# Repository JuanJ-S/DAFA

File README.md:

# DAFA
Dispositivo de Análisis de Fugas de Agua
# Integrantes
 - Wilson David Cortes Gonzales
 - Juan Camilo Forero Castillo
 - Andres Felipe Martinez Roa
 - Fedor Santiago Palacios Hernandez
 - Juan José Santos Pineda
 - David Valero Garzon
# Descripción
Conjunto de sensores conectados a un microcontrolador central (ESP32), que monitorean el caudal y presión del agua en puntos especificos de un sistema de tuberias. El ESP32 se conecta mediante wifi a Blynk, en donde analizan los datos dados por los sensores y se determina si estan dentro de los limites establecidos. Si los valores estan por debajo de lo permitido, se interpreta una posible fuga o conexión no registrada en el sistema, lo cual hará que el dispositivo de una alerta.
# Palabras Clave
 - Perdida de Agua
 - Internet de las Cosas
 - Sensores 
 - ESP 32
 - Gestión Hídrica
 - Sostenibilidad
# Poster
Pendiente -> ¿Como que poster :c?
# Banner de Implementación del Proyecto
En proceso. Imagen preliminar

# Video del Proyecto
Explicacion de: 
    - Problematica
    - Solución Planteada
    - Criterios para la toma de soluciones
    - Funcionamiento del proyecto para el usuario
    - Recomendaciones y Conclusiones

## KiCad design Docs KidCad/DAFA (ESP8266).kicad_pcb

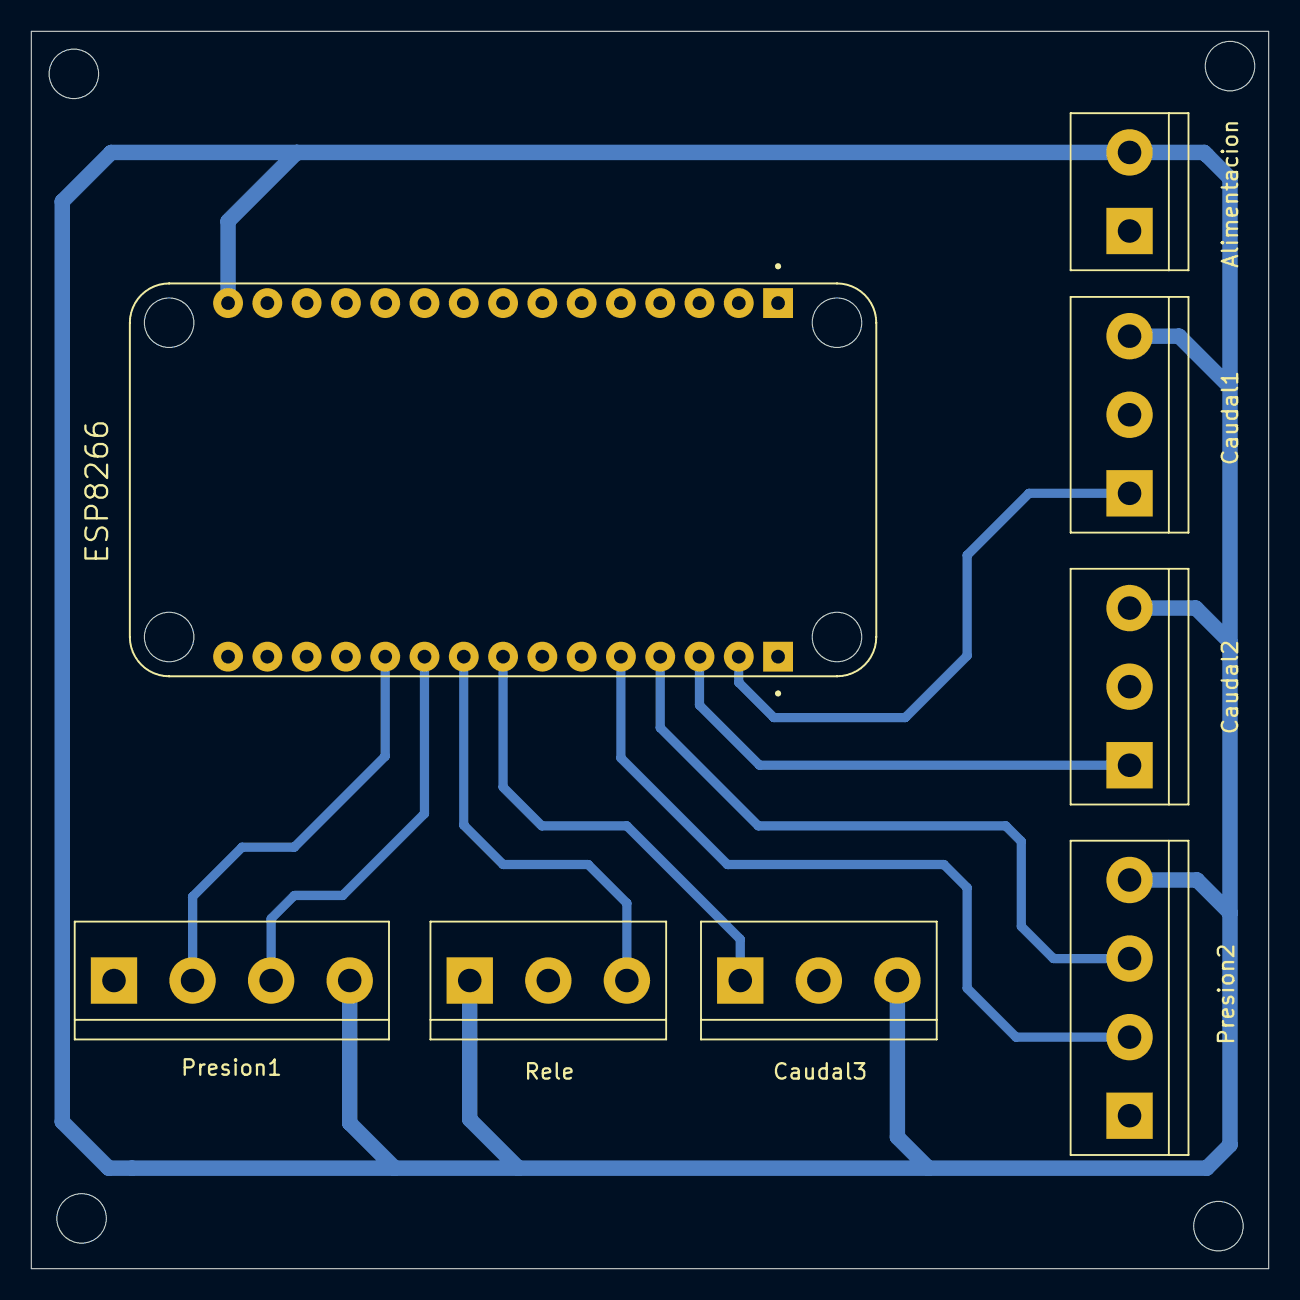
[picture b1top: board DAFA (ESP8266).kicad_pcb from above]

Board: 2 copper layers, 80.0 x 80.0 mm, 8 parts (0 on the bottom side), 10 nets.

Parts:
Alimentacion: Alimentacion; TerminalBlock_bornier-2_P5.08mm
Caudal1: Caudal1; TerminalBlock_bornier-3_P5.08mm
Caudal2: Caudal2; TerminalBlock_bornier-3_P5.08mm
Caudal3: Caudal3; TerminalBlock_bornier-3_P5.08mm
ESP8266: ESP8266; SEEED_113990105
Presion1: Presion1; TerminalBlock_bornier-4_P5.08mm
Presion2: Presion2; TerminalBlock_bornier-4_P5.08mm
Rele: Rele; TerminalBlock_bornier-3_P5.08mm

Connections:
+5V: Alimentacion.2, Caudal1.3, Caudal2.3, Caudal3.3, ESP8266.J1_15 (VIN), Presion1.4, Presion2.4, Rele.1
/Ca04: Caudal2.1, ESP8266.J2_3 (D2)
/Ca05: Caudal1.1, ESP8266.J2_2 (D1)
/Ca14: Caudal3.1, ESP8266.J2_8 (D5)
/Clk02: ESP8266.J2_5 (D4), Presion2.2
/Clk15: ESP8266.J2_11 (D8), Presion1.2
/Dat00: ESP8266.J2_4 (D3), Presion2.3
/Dat13: ESP8266.J2_10 (D7), Presion1.3
/Rele12: ESP8266.J2_9 (D6), Rele.3
GND: Alimentacion.1, Caudal1.2, Caudal2.2, Caudal3.2, ESP8266.J1_10 (GND), ESP8266.J1_14 (GND), ESP8266.J2_7 (GND), ESP8266.J2_14 (GND), Presion1.1, Presion2.1, Rele.2

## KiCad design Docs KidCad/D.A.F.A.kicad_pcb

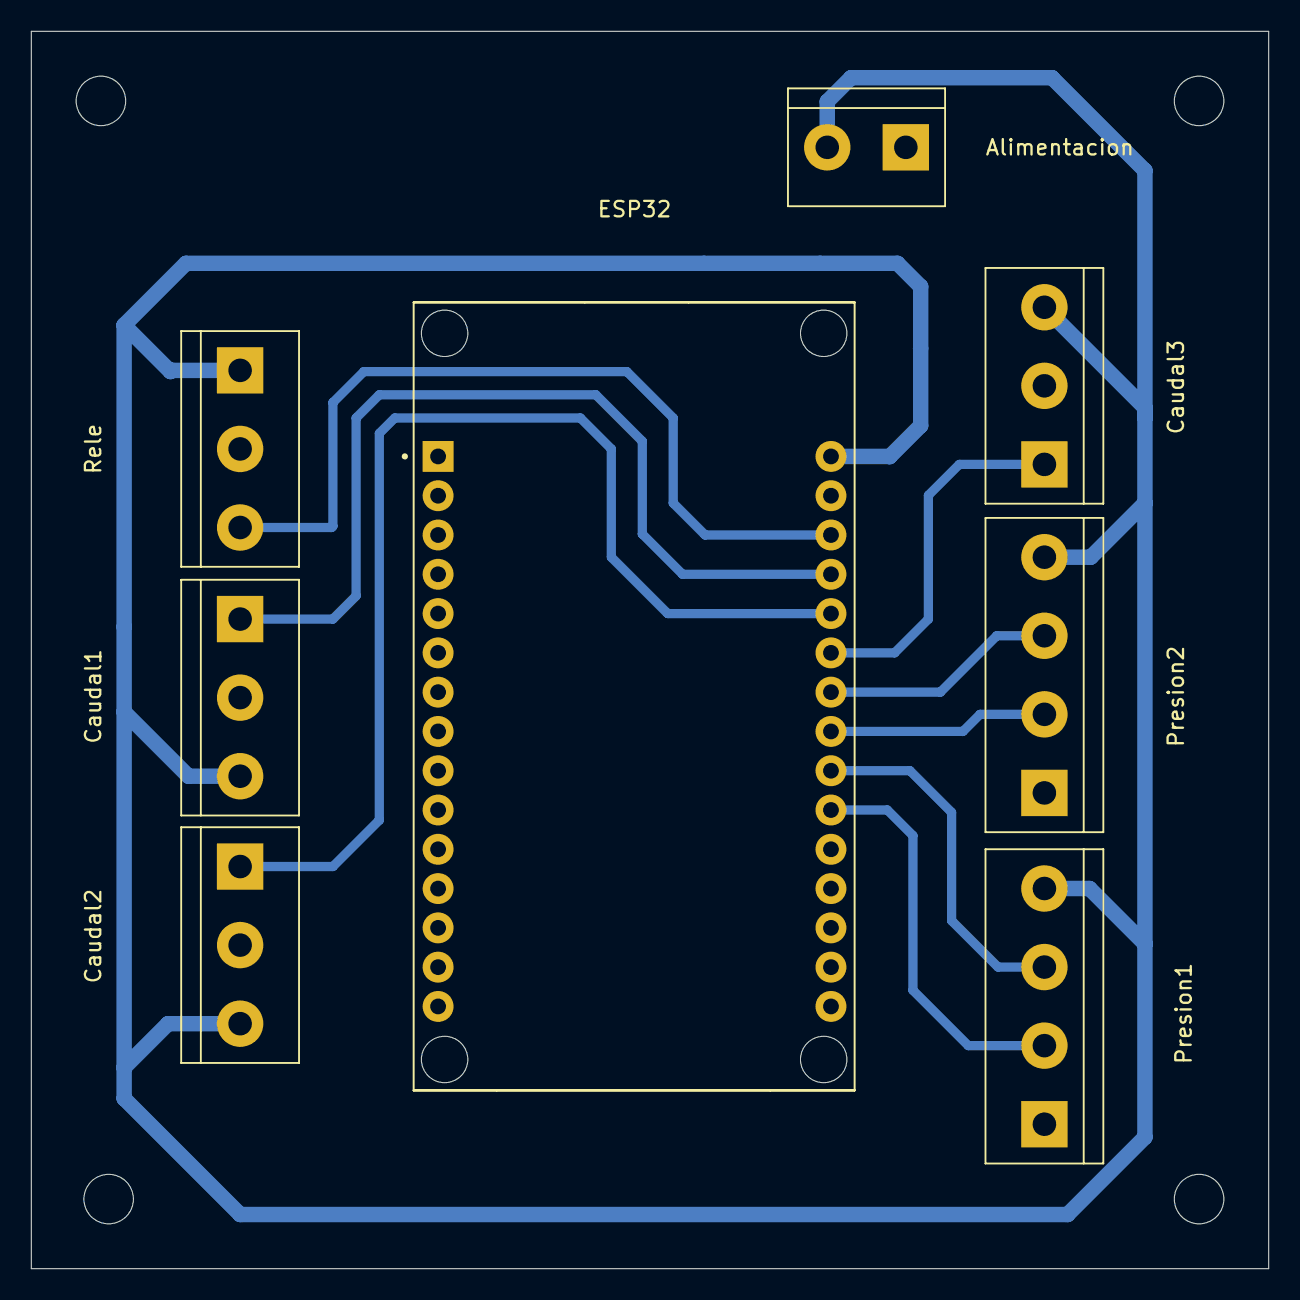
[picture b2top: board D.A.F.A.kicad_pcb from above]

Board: 2 copper layers, 80.0 x 80.0 mm, 8 parts (0 on the bottom side), 10 nets.

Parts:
Alimentacion: Alimentacion; TerminalBlock_bornier-2_P5.08mm
Caudal1: Caudal1; TerminalBlock_bornier-3_P5.08mm
Caudal2: Caudal2; TerminalBlock_bornier-3_P5.08mm
Caudal3: Caudal3; TerminalBlock_bornier-3_P5.08mm
ESP32: ESP32-DEVKIT-V1; MODULE_ESP32_DEVKIT_V1
Presion1: Presion1; TerminalBlock_bornier-4_P5.08mm
Presion2: Presion2; TerminalBlock_bornier-4_P5.08mm
Rele: Rele; TerminalBlock_bornier-3_P5.08mm

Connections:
+5V: Alimentacion.2, Caudal1.3, Caudal2.3, Caudal3.3, ESP32.30 (VIN), Presion1.4, Presion2.4, Rele.1
/Ca12: Caudal1.1, ESP32.27 (D12)
/Ca14: Caudal2.1, ESP32.26 (D14)
/Ca27: Caudal3.1, ESP32.25 (D27)
/Clk25: ESP32.23 (D25), Presion2.2
/Clk32: ESP32.21 (D32), Presion1.2
/Dat26: ESP32.24 (D26), Presion2.3
/Dat33: ESP32.22 (D33), Presion1.3
/Rele13: ESP32.28 (D13), Rele.3
GND: Alimentacion.1, Caudal1.2, Caudal2.2, Caudal3.2, ESP32.2 (GND), ESP32.29 (GND), Presion1.1, Presion2.1, Rele.2

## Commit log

2025-07-14 Ampliación Primera Pagina(?
    Agregue los nombres de los integrantes, de paso experimento como funciona toda esta vaina
2025-07-14 2do Avance
    Descripción, palabra claves y algunas imagenes
2025-07-14 Corrección subida de imagen
    Aprendiendo a añadir imagenes
2025-07-14 Completado pagina 1
    Falta subir imagenes y video requerido
2025-07-14 Anadir Diagrama de Caja Negra
    Eso mismo
2025-07-14 Diagrama Tecnologico
2025-07-22 Cambio Diagrama tecnologico a png
2025-07-23 Imágenes Diseño Case
2025-07-23 esquematicos
2025-07-23 Poster
2025-07-23 Nuevo banner
2025-07-23 Ajuste de poster
2025-07-23 Evidencias
2025-07-23 Proceso PCB
2025-07-24 Documentos del diseño de la pcb en kitcad
